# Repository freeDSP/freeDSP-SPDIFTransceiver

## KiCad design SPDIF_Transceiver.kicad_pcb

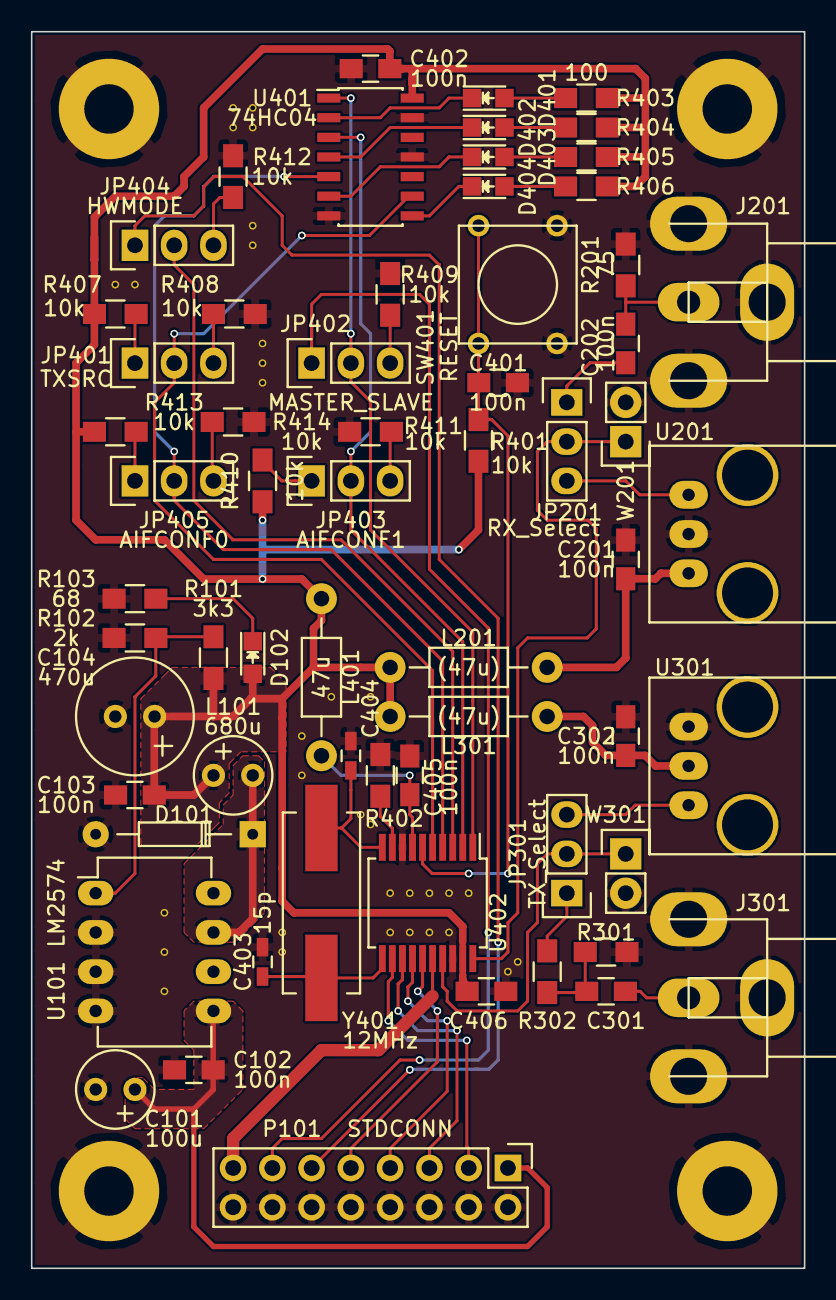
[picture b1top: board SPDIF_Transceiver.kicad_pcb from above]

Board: 2 copper layers, 50.0 x 80.0 mm, 63 parts (0 on the bottom side), 50 nets.

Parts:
C101: 100u; Elko_vert_11x5mm_RM2.5_CopperClear
C102, C103, C201, C202, C301, C302, C401, C402, C405, C406: 100n; C_0805_HandSoldering
C104: 470u; Elko_vert_11.2x7.5mm_RM2.5_CopperClear
C403, C404: 15p; C_0603_HandSoldering
D101: D_Schottky; Diode_DO-35_SOD27_Horizontal_RM10
D102: Green; LED-0805
D401, D402, D403, D404: Yellow; LED-0805
J201: SPDIF_IN; CB-5
J301: SPDIF_OUT; CB-5
JP201: RX_Select; Pin_Header_Straight_1x03
JP301: TX_Select; Pin_Header_Straight_1x03
JP401: TXSRC; Pin_Header_Straight_1x03
JP402: MASTER_SLAVE; Pin_Header_Straight_1x03
JP403: AIFCONF1; Pin_Header_Straight_1x03
JP404: HWMODE; Pin_Header_Straight_1x03
JP405: AIFCONF0; Pin_Header_Straight_1x03
L101: 680u; Elko_vert_11x5mm_RM2.5_CopperClear
L201, L301: (47u); Resistor_Horizontal_RM10mm
L401: 47u; Resistor_Horizontal_RM10mm
P101: STDCONN; Pin_Header_Straight_2x08
R101: 3k3; R_0805_HandSoldering
R102: 2k; R_0805_HandSoldering
R103: 68; R_0805_HandSoldering
R201: 75; R_0805_HandSoldering
R301: 110; R_0805_HandSoldering
R302: 210; R_0805_HandSoldering
R401, R407, R408, R409, R410, R411, R412, R413, R414: 10k; R_0805_HandSoldering
R402: 50; R_0805_HandSoldering
R403, R404, R405, R406: 100; R_0805_HandSoldering
SW401: RESET; SW_PUSH_SMALL
U101: LM2574; DIP-8_W7.62mm_LongPads
U201: TORX147; TOxx147
U301: TOTX147; TOxx147
U401: 74HC04; SOIC-14_3.9x8.7mm_Pitch1.27mm
U402: WM8804; SSOP-20_5.3x7.2mm_Pitch0.65mm
W201: SPDIF_RX_TEST; Pin_Header_Straight_1x02
W301: SPDIF_TX_TEST; Pin_Header_Straight_1x02
Y401: 12MHz; Crystal_HC49-SD_SMD

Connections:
+3V3: C103.1, C104.1, C402.1, C406.1, D102.2, L101.1, L201.1, L301.1, L401.1, R101.1, R401.1, R403.2, R404.2, R405.2, R406.2, R407.1, R410.1, R413.1, U401.14, U402.19
+12V: C101.1, C102.1, P101.1, U101.5
/SPDIF_Input/SPDIF_RX: JP201.2, U402.20, W201.1
/SPDIF_Output/SPDIF_TX: JP301.2, U402.17, W301.1
/Transceiver/AIFCONF0: JP405.2, U401.5, U402.4
/Transceiver/AIFCONF1: JP403.2, U401.3, U402.2
/Transceiver/BCLK: P101.7, U402.14
/Transceiver/DIN: P101.5, U402.13
/Transceiver/DOUT: P101.3, U402.12
/Transceiver/HWMODE: JP404.2, U402.3
/Transceiver/LRCLK: P101.9, U402.15
/Transceiver/MASTER_SLAVE: JP402.2, U401.1, U402.1
/Transceiver/MCLK: P101.15, U402.16
/Transceiver/PVDD: C405.1, L401.2, U402.7
/Transceiver/RESET: C401.1, R401.2, SW401.1, U402.6
/Transceiver/SCL: JP402.1, P101.13
/Transceiver/SDA: JP404.1, P101.11
/Transceiver/TXSRC: JP401.2, U401.9, U402.5
GND: C101.2, C102.2, C103.2, C104.2, C201.1, C302.1, C401.2, C402.2, C403.2, C404.2, C405.2, C406.2, D101.2, J201.2, J301.2, P101.2, P101.4, P101.6, P101.8, P101.10, P101.12, P101.14, P101.16, R102.2, R103.2, R201.2, R301.2, R402.2, R408.2, R409.2, R411.2, R412.2, R414.2, SW401.2, U101.2, U101.3, U101.4, U201.2, U301.1, U401.7, U401.11, U401.13, U402.8, U402.18, W201.2, W301.2
unnamed: C201.2, L201.2, U201.3
unnamed: C202.1, J201.1, R201.1
unnamed: C202.2, JP201.1
unnamed: C301.1, J301.1
unnamed: C301.2, R301.1, R302.2
unnamed: C302.2, L301.2, U301.2
unnamed: C403.1, U402.11, Y401.1
unnamed: C404.1, U402.10, Y401.2
unnamed: D101.1, L101.2, U101.7
unnamed: D102.1, R103.1
unnamed: D401.1, U401.2
unnamed: D401.2, R403.1
unnamed: D402.1, U401.4
unnamed: D402.2, R404.1
unnamed: D403.1, U401.6
unnamed: D403.2, R405.1
unnamed: D404.1, U401.8
unnamed: D404.2, R406.1
unnamed: JP201.3, U201.1
unnamed: JP301.1, R302.1
unnamed: JP301.3, U301.3
unnamed: JP401.1, R407.2
unnamed: JP401.3, R408.1
unnamed: JP402.3, R409.1
unnamed: JP403.1, R410.2
unnamed: JP403.3, R411.1
unnamed: JP404.3, R412.1
unnamed: JP405.1, R413.2
unnamed: JP405.3, R414.1
unnamed: R101.2, R102.1, U101.1
unnamed: R402.1, U402.9

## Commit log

2016-05-15 Created Schematic.
2016-05-16 Added board layout.
2016-05-16 Little changes, added Gerber Files.
2016-05-30 Added BOM
2016-11-18 pre update
